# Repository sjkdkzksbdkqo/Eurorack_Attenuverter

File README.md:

# Eurorack_Attenuverter
 A simple 2 Channel attenuverter

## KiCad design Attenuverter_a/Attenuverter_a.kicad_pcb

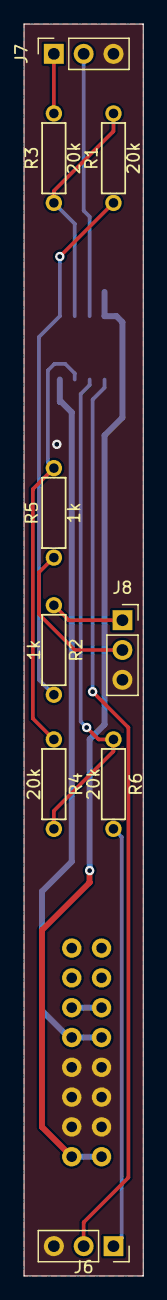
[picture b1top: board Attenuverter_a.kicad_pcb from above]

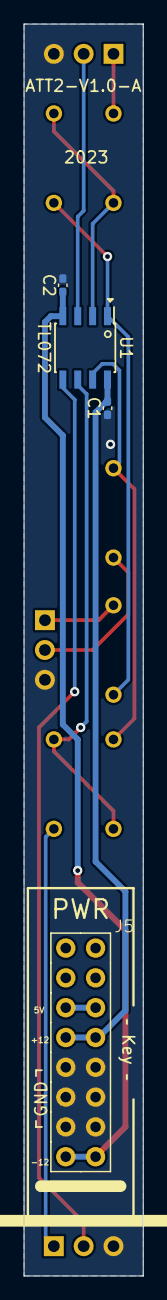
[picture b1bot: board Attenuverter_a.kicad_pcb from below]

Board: 2 copper layers, 10.2 x 106.7 mm, 13 parts (4 on the bottom side), 14 nets.

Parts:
C1, C2: 100nf; C_0402_1005Metric_Pad0.74x0.62mm_HandSolder
J5: PWR; Pins_2x08_2.54mm_TH_EuroPower_Shrouded
J6, J7, J8: Conn_01x03; PinSocket_1x03_P2.54mm_Vertical
R1, R3, R4, R6: 20k; R_Axial_DIN0207_L6.3mm_D2.5mm_P7.62mm_Horizontal
R2, R5: 1k; R_Axial_DIN0207_L6.3mm_D2.5mm_P7.62mm_Horizontal
U1: TL072; SOIC-8_3.9x4.9mm_Pitch1.27mm

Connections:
+5V: J5.5 (+12V), J5.6
+12V: C1.2, J5.7 (12V), J5.8 (+12V), U1.8 (V+)
+in_A: J7.2, U1.3 (+)
+in_B: J6.2, U1.5 (+)
-12V: C2.1, J5.15 (-12V), J5.16, U1.4 (V-)
GND: C1.1, C2.2, J5.9 (GND), J5.10 (GND), J5.11 (GND), J5.12 (GND), J5.13 (-12), J5.14 (-12V), J6.3, J7.3, J8.3
unnamed: R1.2, R2.1, U1.1
unnamed: R4.2, R5.1, U1.7
unnamed: R1.1, R3.2, U1.2 (-)
unnamed: R4.1, R6.2, U1.6 (-)
Sig_in_A: J7.1, R3.1
Sig_in_B: J6.1, R6.1
Sig_out_A: J8.1, R2.2
Sig_out_B: J8.2, R5.2

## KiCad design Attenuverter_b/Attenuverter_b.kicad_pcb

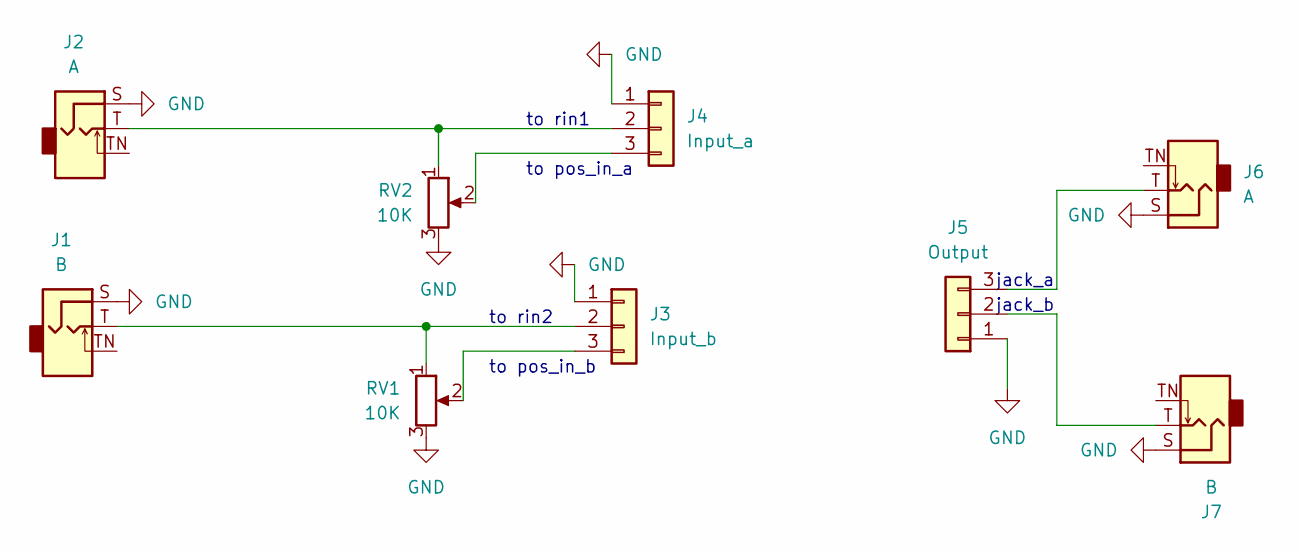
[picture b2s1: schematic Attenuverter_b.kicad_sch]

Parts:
J1, J7: B; Jack_3.5mm_QingPu_WQP-PJ398SM_Vertical_CircularHoles
J2, J6: A; Jack_3.5mm_QingPu_WQP-PJ398SM_Vertical_CircularHoles
J3: Input_b; PinHeader_1x03_P2.54mm_Vertical; Part Number 1-0301FBV0T
J4: Input_a; PinHeader_1x03_P2.54mm_Vertical; Part Number 1-0301FBV0T
J5: Output; PinHeader_1x03_P2.54mm_Vertical; Part Number 1-0301FBV0T
RV1, RV2: 10K; Pot_9mm_DShaft

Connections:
GND: J1.S, J2.S, J3.1, J4.1, J5.1, J6.S, J7.S, RV1.3, RV2.3
unnamed: J1.T, J3.2, RV1.1
unnamed: J3.3, RV1.2
unnamed: J2.T, J4.2, RV2.1
unnamed: J4.3, RV2.2
unnamed: J5.2, J7.T
unnamed: J5.3, J6.T

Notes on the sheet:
jack_b
to pos_in_a
jack_a
to rin2
to rin1
to pos_in_b

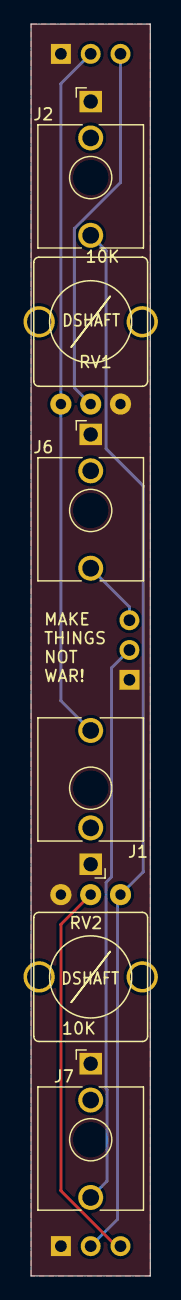
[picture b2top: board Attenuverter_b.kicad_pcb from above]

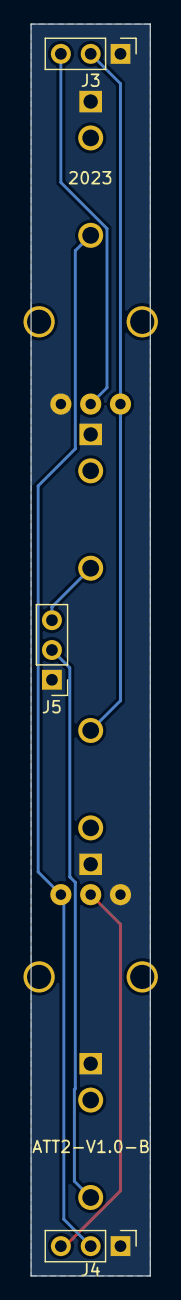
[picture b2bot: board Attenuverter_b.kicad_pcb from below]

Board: 2 copper layers, 10.2 x 106.7 mm, 9 parts (3 on the bottom side), 7 nets.
